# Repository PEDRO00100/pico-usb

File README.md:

> [!WARNING]
> ### ⚠️ LEGAL DISCLAIMER & TERMS OF USE
> 
> This hardware device, firmware, and its accompanying software suite are developed and provided **strictly for educational purposes, authorized laboratory environments, and professional security auditing.**
> 
> By building, accessing, or utilizing this tool, you acknowledge and agree to the following:
> 
> * **Authorized Use Only:** You must obtain explicit, written consent from the infrastructure or system owner before engaging in any security testing, payload injection, or assessment.
> * **No Liability:** The creators, contributors, and maintainers of this project assume **absolute no liability** and are not responsible for any direct or indirect damage, data loss, misuse, or illegal activities resulting from the deployment of this device.
> * **End-User Responsibility:** It is solely your responsibility to ensure compliance with all applicable local, state, and federal laws. Any use of this tool for malicious intent, unauthorized access, or covert data exfiltration is strictly prohibited.

## ⚙️ System Architecture & Operation

This project is a hardware-based security auditing and penetration testing tool (HID Injection Engine) built around the **RP2040** microcontroller. Unlike traditional USB injection scripts that require hardcoding and recompiling firmware for every assessment, this device operates as an autonomous, dynamic execution engine. It reads attack scripts directly from an external MicroSD card and allows instant, on-the-fly selection of up to 16 different payloads via hardware switching.

---

### 1. Hardware & Peripheral Mapping

The PCB layout is engineered for signal integrity, prioritizing short trace lengths for high-speed SPI bus lines while keeping digital control switches isolated. The GPIO pin assignment on the RP2040 is structured as follows:

| Physical Peripheral | RP2040 Pin | System Function / Role | Electrical Logic |
| :--- | :---: | :--- | :--- |
| **Setup Mode Switch (`GP0/DEV`)** | `GP0` | Toggles between Development Mode & Attack Mode | Internal Pull-Up (`GND = Dev`) |
| **DIP Switch (Bit 0 - LSB)** | `GP2` | Binary Payload Selector (`payload1Pin` / `SWD-1`) | Active-Low (`GND = 1`) |
| **DIP Switch (Bit 1)** | `GP3` | Binary Payload Selector (`payload2Pin` / `SWD-2`) | Active-Low (`GND = 1`) |
| **DIP Switch (Bit 2)** | `GP4` | Binary Payload Selector (`payload3Pin` / `SWD-3`) | Active-Low (`GND = 1`) |
| **DIP Switch (Bit 3 - MSB)** | `GP5` | Binary Payload Selector (`payload4Pin` / `SWD-4`) | Active-Low (`GND = 1`) |
| **MicroSD SPI (MISO)** | `GP16` | Data receive from external storage | SPI0 Bus |
| **MicroSD SPI (CS)** | `GP17` | Chip Select / SD card activation | Digital Output |
| **MicroSD SPI (SCK)** | `GP18` | Bus clock synchronization | SPI0 Bus |
| **MicroSD SPI (MOSI)** | `GP19` | Data transmit to external storage | SPI0 Bus |

*(Note: Additional GPIO pins such as `GP22` are routed on the PCB layout for secondary applications or future expansion, but are omitted from active execution loops to streamline automated payload delivery).*

#### 🔘 Onboard Physical Control Buttons
The device incorporates three dedicated tactile buttons for system management and firmware operations:
* **`BOOTSEL` Button:** Connected directly to the RP2040 bootrom interface. Holding this button while plugging the device into a host forces entry into USB Mass Storage bootloader mode for flashing or updating the core CircuitPython firmware (`.uf2` files).
* **`RUN` / `RST` Button:** Triggers a hard electrical reset of the RP2040 microcontroller without needing to physically unplug the USB connector, enabling rapid rebooting after switching payloads.
* **`DEV MODE` Button (`GP0`):** Pulls `GP0` to ground (`GND`). When engaged during boot, it prevents automated payload execution and mounts the internal `CIRCUITPY` drive for safe script editing.

#### 🔌 Dual-Head USB Interface & Protection
The hardware features a versatile **Dual-Head USB architecture**, integrating both **USB-A** and **USB-C** connectors directly onto the PCB edge. This allows native insertion into legacy desktops, modern laptops, servers, and mobile devices without requiring external adapters. 
* **ESD Protection:** The data lines (`D+` / `D-`) include onboard electrical protections and transient voltage suppression to safeguard the microcontroller against static discharges during rapid field insertion.
* **⚠️ Critical Safety Rule:** The dual connectors share the same internal USB data bus. **Never connect both USB-A and USB-C ports simultaneously to two different host devices or power sources**, as this could cause bus contention or electrical back-feeding.

---

### 2. Binary Payload Selector (4-Bit DIP Switch)

To eliminate the need for reprogramming the device between different engagement scenarios, the board features an onboard 4-position DIP switch (`A6H-4101`) operating on **pure binary decoding**.

Each switch pin is configured with internal pull-up resistors (Active-Low logic). Moving a switch to the **ON** position bridges the circuit to Ground (`GND`), which the firmware decodes as a logical `1` for that specific bit position.

```text
Bit 3 (MSB)   Bit 2       Bit 1       Bit 0 (LSB)
  [GP5]       [GP4]       [GP3]       [GP2]
  Value: 8    Value: 4    Value: 2    Value: 1

```

* **Combination `0000` (All OFF):** Executes the default script located at `/sd/payload.dd`.
* **Combinations `0001` through `1111` (1 to 15):** Sums the active bit values in powers of 2 and dynamically routes execution to the numbered script on the MicroSD card (from `/sd/payload1.dd` up to `/sd/payload15.dd`).

---

### 3. Operating Modes & USB Stealth Spoofing

The USB enumeration profile is strictly managed by `boot.py` **before** the target operating system (Windows, macOS, or Linux) initializes the peripheral. The operating mode is governed by the state of the `GP0` tactile button/switch:

#### 🟢 Development Mode (`GP0` connected to GND)

* **Purpose:** Script editing, live debugging, and system maintenance.
* **USB Profile:** Habilitates standard USB Mass Storage (exposing the internal `CIRCUITPY` drive), Serial CDC (REPL console), and HID keyboard interfaces. Automated attack execution is safely bypassed.

#### 🔴 Attack / Stealth Mode (`GP0` floating / Unpressed)

* **Purpose:** Active field auditing and Endpoint Detection & Response (EDR / DLP) evasion.
* **USB Profile:** The firmware executes `storage.disable_usb_drive()`, completely hiding internal Flash memory from the host OS and disabling Serial/MIDI endpoints (`usb_cdc.disable()`, `usb_midi.disable()`).
* **Identity Spoofing:** To prevent triggering vendor-specific blocklists while adhering to safe open-source distribution standards (BYOC - *Bring Your Own Configuration*), the device overrides its hardware descriptors using the open community VID **`0x1209`** (pid.codes) and generic keyboard PID **`0x0001`**:

```python
# Hardware descriptor override defined in boot.py
supervisor.set_usb_identification(
    vid=0x1209,         # Open-Source Community VID (pid.codes)
    pid=0x0001,         # Generic Keyboard PID
    manufacturer="Generic",
    product="USB Keyboard"
)

```

> ⚠️ **Tactical Advantage:** When plugged into a host system in Attack Mode, the operating system **strictly enumerates a generic HID USB Keyboard**. No storage drives are mounted, no COM ports appear in Device Manager, and no Raspberry Pi / Adafruit hardware signatures are exposed.

---

### 4. Asynchronous Execution Engine & Resilience

The core execution engine (`code.py`) is built around asynchronous event loops (`asyncio`). This allows the microcontroller to handle concurrent background tasks—such as button debouncing, filesystem polling, and monitoring host keyboard lock LEDs (Caps/Num/Scroll Lock) for data exfiltration—without causing latency or blocking keystroke injection.

To guarantee field reliability and prevent kernel panics during live deployments, the firmware implements multiple defensive architecture layers:

1. **Zero-RAM Allocation Filesystem Polling:** To check for the presence of payload files on the MicroSD card without fragmenting the microcontroller's limited heap memory, the engine avoids memory-heavy directory listings (`os.listdir()`). Instead, it performs direct, low-overhead FAT32 metadata queries using `os.stat()`.
2. **3-Tier Fallback Routing:** If an indexed script cannot be read, the execution pipeline gracefully degrades through three safety tiers to ensure the assessment does not fail silently:
* *Tier 1:* Attempts to execute the exact binary path selected by the DIP switch (e.g., `/sd/payload5.dd`).
* *Tier 2:* If the target file is missing, it falls back automatically to the standard default script (`/sd/payload.dd`).
* *Tier 3:* If the default script is also missing, it performs an emergency scan of the MicroSD card root and executes the first available `.dd` payload found.

3. **Hardware Kill-Switch:** During the boot sequence, if the engine detects a file named `loot.bin` in the root directory, it immediately aborts all keystroke injection routines to prevent accidental exfiltration overrides or execution loops.

## 💾 Firmware & Software Installation Guide

Setting up the device is divided into two straightforward phases: flashing the base interpreter (CircuitPython) and loading the attack and decoding engine. Once this process is complete, the microcontroller's execution logic will be permanently configured.

---

### Step 1: Installing the Core Engine (CircuitPython)

To enable the RP2040 microcontroller to interpret attack scripts in real time, you must install the base CircuitPython firmware:

1. **Bootloader Mode:** Press and hold the onboard **`BOOTSEL`** physical button while plugging the USB cable into your computer.
2. **RPI-RP2 Drive:** Release the button once plugged in. Your operating system will automatically mount a mass storage drive named `RPI-RP2`.
3. **Flashing:** Download the latest official release of **CircuitPython 10.x** (`.uf2` file format) for the Raspberry Pi Pico / RP2040 and drag the file directly into the `RPI-RP2` drive.
4. **Automatic Reboot:** Once the copy completes, the drive will automatically eject, and the microcontroller will reboot, creating a new flash drive named **`CIRCUITPY`**.

---

### Step 2: Loading the Attack Engine & Dependencies

Once the `CIRCUITPY` drive is available, you must transfer the core operating logic and hardware libraries. Navigate to the `Software/` directory within this repository, which contains the exact system package:

```text
Software/
├── boot.py             # Hardware USB Profile & Stealth Spoofing Manager
├── boot_out.txt        # System boot log (Auto-generated by CircuitPython)
├── code.py             # Asynchronous Core Kernel & Execution Loop
├── duckyinpython.py    # DuckyScript Parser & Payload Execution Engine
├── lib/                # Required CircuitPython libraries (HID, Debouncer, etc.)
├── LICENSE             # GPLv2 License
├── pins.py             # Hardware GPIO Pin Mapping & DIP Switch Config
├── sd/                 # Example payload directory (For external MicroSD card)
└── settings.toml       # Runtime configuration file

```

#### 📦 File Transfer Protocol:

1. **Internal Flash (`CIRCUITPY` drive):**
* Select and copy all core Python scripts (`boot.py`, `code.py`, `duckyinpython.py`, `pins.py`, `settings.toml`, and `LICENSE`).
* **⚠️ CRITICAL - The `lib/` folder:** You **must** copy the entire **`lib/`** directory into the root of the `CIRCUITPY` drive. This folder contains essential drivers (`adafruit_hid`, `adafruit_debouncer`, etc.) required for keystroke injection and tactile button reading.
* *(Note: You can ignore `boot_out.txt`, as the microcontroller will automatically regenerate this log file on its next boot).*

2. **External Storage (MicroSD Card):**
* Take the contents inside the **`sd/`** folder (e.g., your `.dd` payload files) and copy them directly to the root of your FAT32-formatted **MicroSD card**.
* Insert the MicroSD card into the onboard SPI slot (`J3`). When the RP2040 boots, `code.py` will automatically mount this physical card at the `/sd` system path.

---

### Step 3: Access Management & Safe Mode (Critical!)

As soon as the system files are copied over, `boot.py` will take absolute control of the board's USB interfaces on every subsequent boot. It is crucial to understand the following tactical behavior before unplugging the cable:

> 🚨 **AUTOMATIC INJECTION WARNING:**
> From this moment forward, **every time you plug the device into a USB port normally, it will boot in Attack Mode (Stealth Mode)**. This means the `CIRCUITPY` drive will completely disappear from your operating system, and the payload selected via the DIP switch on the MicroSD card **will execute automatically and immediately**.

#### 🛠️ How to re-access the `CIRCUITPY` drive to edit code?

To prevent the attack script from triggering and to mount the internal storage drive back onto your computer (e.g., to debug code or update core scripts), you must engage the hardware safety override:

1. **Press and hold the `DEV MODE` (`GP0`) button** on the board.
2. While holding the button down, **plug the USB cable** into your computer.
3. Once plugged in, you can safely release the button.
4. **Result:** The microcontroller detects the ground connection on pin `GP0`, aborts automated payload execution, and safely exposes the `CIRCUITPY` drive and Serial REPL console on your screen in safe development mode.

## 🛠️ Hardware Compatibility & DIY Protoboard Build

While this project features a custom-designed, dedicated PCB with integrated dual-head USB connectors and ESD protection, the core software suite is **100% compatible with standard, off-the-shelf Raspberry Pi Pico** boards (or any generic RP2040 development board running CircuitPython).

If you are prototyping on a breadboard or building a custom DIY injection tool using an original Raspberry Pi Pico, you can deploy this firmware without modifying a single line of code. You simply need to manually wire the external modules according to the hardware mapping defined in `pins.py`:

### 📌 DIY Wiring Checklist for Standard Pico:
* **MicroSD Card Module:** Wire a 3.3V SPI MicroSD breakout board directly to the RP2040's **SPI0 bus** (`MISO` -> `GP16`, `CS` -> `GP17`, `SCK` -> `GP18`, and `MOSI` -> `GP19`).
* **4-Bit Binary DIP Switch:** Connect four mechanical switches (or simple jumper wires) between ground (`GND`) and pins **`GP2`**, **`GP3`**, **`GP4`**, and **`GP5`**. When closed (grounded), the internal pull-up resistor drops to `0V`, which the software decodes as an active binary `1`.
* **Development Mode Safety Jumper (`GP0`):** You **must** wire a tactile button or jumper wire between **`GP0`** and **`GND`**. This is critical: without this physical override, an off-the-shelf Pico will permanently boot in Stealth Attack Mode, hiding the USB drive and locking you out of the REPL console.

---

## 📂 MicroSD Payload Structure & Binary Mapping

The execution engine searches the root directory of the FAT32-formatted MicroSD card for standard DuckyScript (`.dd`) payload files. To utilize the hardware DIP switch, name your scripts following this exact binary convention:

| DIP Switch State (`SW4` -> `SW1`) | Binary Value | Target Payload Path | Description / Engagement Use Case |
| :---: | :---: | :--- | :--- |
| `OFF` · `OFF` · `OFF` · `OFF` | `0000` (0) | `/sd/payload.dd` | Default fallback / Standard assessment payload |
| `OFF` · `OFF` · `OFF` · `ON`  | `0001` (1) | `/sd/payload1.dd` | Quick reconnaissance / System info enumeration |
| `OFF` · `OFF` · `ON`  · `OFF` | `0010` (2) | `/sd/payload2.dd` | Remote access staging / Reverse shell |
| `...` · `...` · `...` · `...` | `1 to 14`  | `/sd/payload3.dd` to `14.dd` | Custom specialized audit scripts |
| `ON`  · `ON`  · `ON`  · `ON`  | `1111` (15)| `/sd/payload15.dd`| Emergency cleanup / Anti-forensic routine |

> 💡 **Tactical Fallback Note:** If you dial a specific binary combination on the DIP switch (e.g., index `5`) but forget to load `/sd/payload5.dd` onto the MicroSD card, the asynchronous engine will not crash. It automatically downgrades to Tier-2 fallback and executes `/sd/payload.dd`, guaranteeing that your field engagement never fails silently.

---

## 📸 Board Designs & Renders

3D renders and PCB layer routing for the **Pico-USB** board.

<table align="center">
  <tr>
    <td align="center">
      <br/>
      <sub><b>3D Front</b></sub>
    </td>
    <td align="center">
      <br/>
      <sub><b>3D Back</b></sub>
    </td>
    <td align="center">
      <br/>
      <sub><b>2D F.Cu</b></sub>
    </td>
    <td align="center">
      <br/>
      <sub><b>2D B.Cu</b></sub>
    </td>
  </tr>
</table>

---

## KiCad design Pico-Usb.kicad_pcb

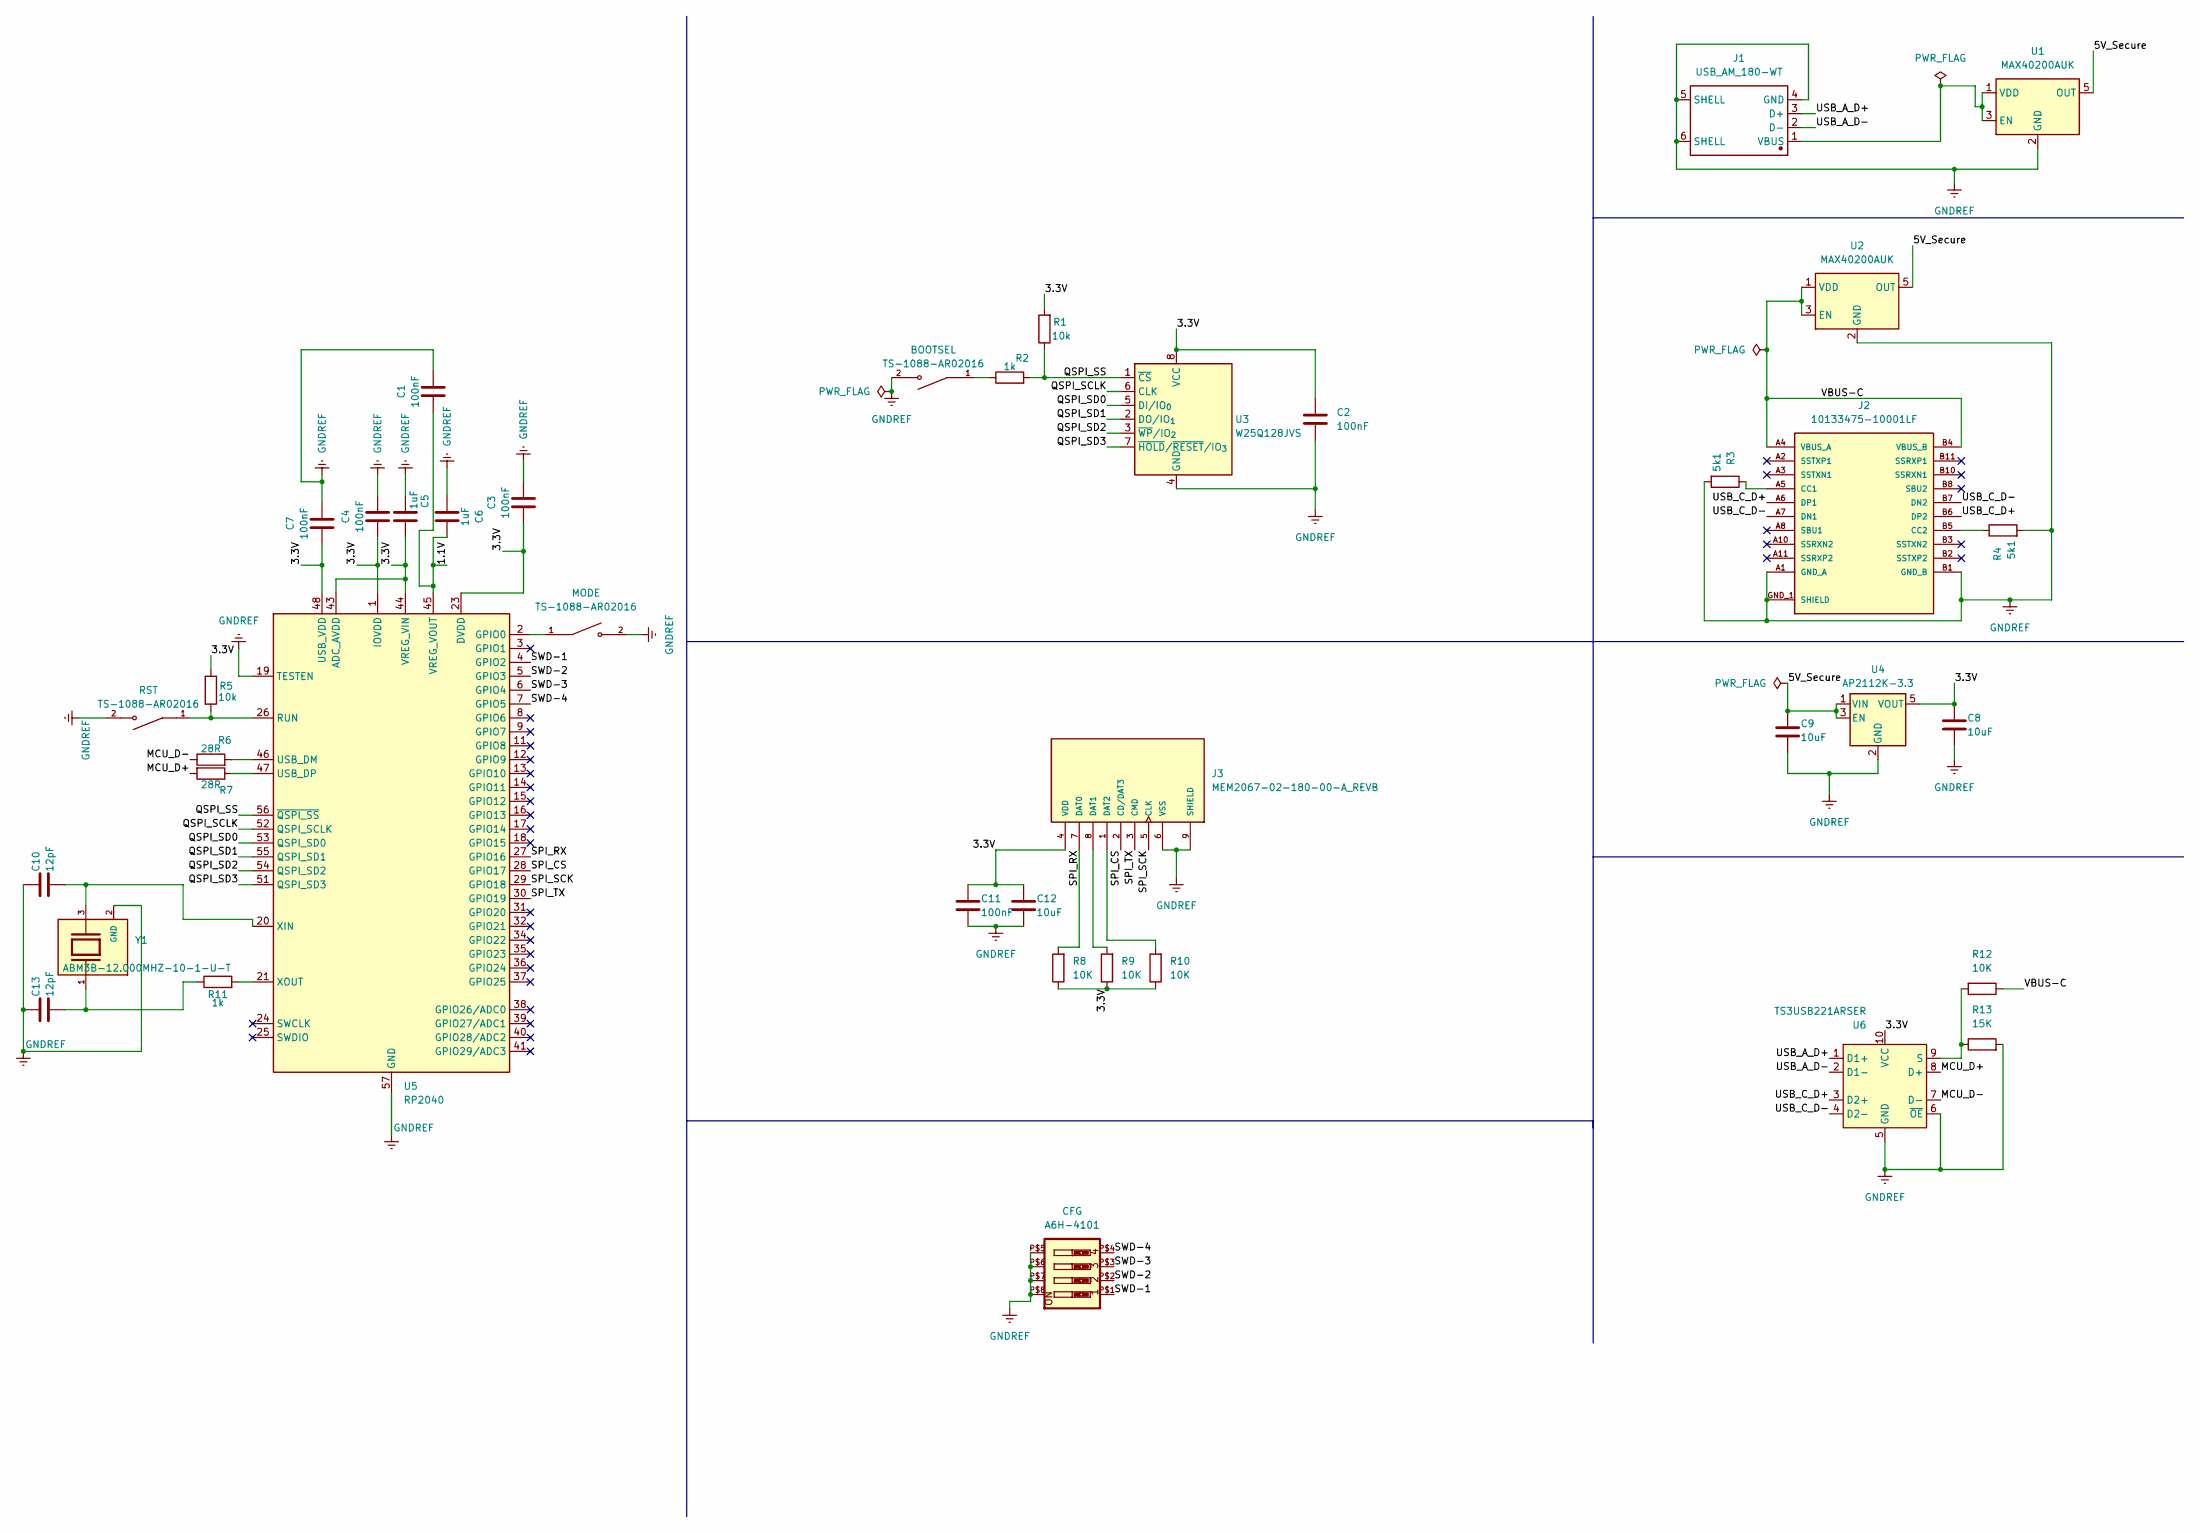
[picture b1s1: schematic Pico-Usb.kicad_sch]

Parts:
BOOTSEL: TS-1088-AR02016; SW_TS-1088-AR02016; PARTREV N/A
C1, C2, C3, C4, C7, C11: 100nF; C_0402_1005Metric
C5, C6: 1uF; C_0402_1005Metric
C8, C9, C12: 10uF; C_0402_1005Metric
C10, C13: 12pF; C_0402_1005Metric
CFG: A6H-4101; A6H-410X
J1: USB_AM_180-WT; USB-AM-180-WT
J2: 10133475-10001LF; Amphenol_USBC_Plug; PARTREV C
J3: MEM2067-02-180-00-A_REVB; GCT_MEM2067-02-180-00-A_REVB
MODE: TS-1088-AR02016; SW_TS-1088-AR02016; PARTREV N/A
R1, R5: 10k; R_0402_1005Metric
R2, R11: 1k; R_0402_1005Metric
R3, R4: 5k1; R_0402_1005Metric
R6, R7: 28R; R_0402_1005Metric
R8, R9, R10, R12: 10K; R_0402_1005Metric
R13: 15K; R_0402_1005Metric
RST: TS-1088-AR02016; SW_TS-1088-AR02016; PARTREV N/A
U1, U2: MAX40200AUK; SOT-23-5
U3: W25Q128JVS; SOIC-8_5.3x5.3mm_P1.27mm
U4: AP2112K-3.3; SOT-23-5
U5: RP2040; QFN-56-1EP_7x7mm_P0.4mm_EP3.2x3.2mm
U6: TS3USB221ARSER; TS3USB221
Y1: ABM3B-12.000MHZ-10-1-U-T; XTAL_ABM3B-12.000MHZ-10-1-U-T; PARTREV 08.25.15

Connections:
/1.1V: C1.1, C6.1, U5.45 (VREG_VOUT)
/3.3V: C2.1, C3.1, C4.1, C5.1, C7.1, C8.1, C11.1, C12.1, J3.4 (VDD), R1.2, R5.1, R8.1, R9.1, R10.1, U3.8 (VCC), U4.5 (VOUT), U5.1 (IOVDD), U5.10 (IOVDD), U5.22 (IOVDD), U5.23 (DVDD), U5.33 (IOVDD), U5.42 (IOVDD), U5.43 (ADC_AVDD), U5.44 (VREG_VIN), U5.48 (USB_VDD), U5.49 (IOVDD), U5.50 (DVDD), U6.10 (VCC)
/5V_Secure: C9.1, U1.5 (OUT), U2.5 (OUT), U4.1 (VIN), U4.3 (EN)
/MCU_D+: R7.2, U6.8 (D+)
/MCU_D-: R6.1, U6.7 (D-)
/QSPI_SCLK: U3.6 (CLK), U5.52 (QSPI_SCLK)
/QSPI_SD0: U3.5 (DI/IO_{0}), U5.53 (QSPI_SD0)
/QSPI_SD1: U3.2 (DO/IO_{1}), U5.55 (QSPI_SD1)
/QSPI_SD2: U3.3 (~WP/IO_{2}), U5.54 (QSPI_SD2)
/QSPI_SD3: U3.7 (~HOLD/~RESET/IO_{3}), U5.51 (QSPI_SD3)
/QSPI_SS: R1.1, R2.2, U3.1 (~CS), U5.56 (~QSPI_SS)
/SPI_CS: J3.2 (CD/DAT3), U5.28 (GPIO17)
/SPI_RX: J3.7 (DAT0), R8.2, U5.27 (GPIO16)
/SPI_SCK: J3.5 (CLK), U5.29 (GPIO18)
/SPI_TX: J3.3 (CMD), U5.30 (GPIO19)
/SWD-1: CFG.P$1, U5.4 (GPIO2)
/SWD-2: CFG.P$2, U5.5 (GPIO3)
/SWD-3: CFG.P$3, U5.6 (GPIO4)
/SWD-4: CFG.P$4, U5.7 (GPIO5)
/USB_A_D+: J1.3 (D+), U6.1 (D1+)
/USB_A_D-: J1.2 (D-), U6.2 (D1-)
/USB_C_D+: J2.A6 (DP1), J2.B6 (DP2), U6.3 (D2+)
/USB_C_D-: J2.A7 (DN1), J2.B7 (DN2), U6.4 (D2-)
GNDREF: BOOTSEL.2, C1.2, C2.2, C3.2, C4.2, C5.2, C6.2, C7.2, C8.2, C9.2, C10.1, C11.2, C12.2, C13.1, CFG.P$5, CFG.P$6, CFG.P$7, CFG.P$8, J1.4 (GND), J1.5 (SHELL), J1.6 (SHELL), J2.A1 (GND_A), J2.A12 (GND_A), J2.B1 (GND_B), J2.B12 (GND_B), J2.GND_1 (SHIELD), J2.GND_2 (SHIELD), J3.6 (VSS), J3.9 (SHIELD), J3.10 (SHIELD), J3.11 (SHIELD), J3.12 (SHIELD), MODE.2, R3.2, R4.2, R13.2, RST.2, U1.2 (GND), U2.2 (GND), U3.4 (GND), U4.2 (GND), U5.19 (TESTEN), U5.57 (GND), U6.5 (GND), U6.6 (~OE), Y1.2 (GND), Y1.4 (GND)
unnamed: BOOTSEL.1, R2.1
unnamed: C13.2, R11.1, Y1.1
unnamed: J2.A5 (CC1), R3.1
unnamed: J2.B5 (CC2), R4.1
unnamed: J3.8 (DAT1), R9.2
unnamed: J3.1 (DAT2), R10.2
unnamed: J1.1 (VBUS), U1.1 (VDD), U1.3 (EN)
unnamed: MODE.1, U5.2 (GPIO0)
unnamed: R5.2, RST.1, U5.26 (RUN)
unnamed: R6.2, U5.46 (USB_DM)
unnamed: R7.1, U5.47 (USB_DP)
unnamed: C10.2, U5.20 (XIN), Y1.3
unnamed: R11.2, U5.21 (XOUT)
unnamed: R12.2, R13.1, U6.9 (S)
VBUS_A: J2.A4 (VBUS_A), J2.A9 (VBUS_A), J2.B4 (VBUS_B), J2.B9 (VBUS_B), R12.1, U2.1 (VDD), U2.3 (EN)

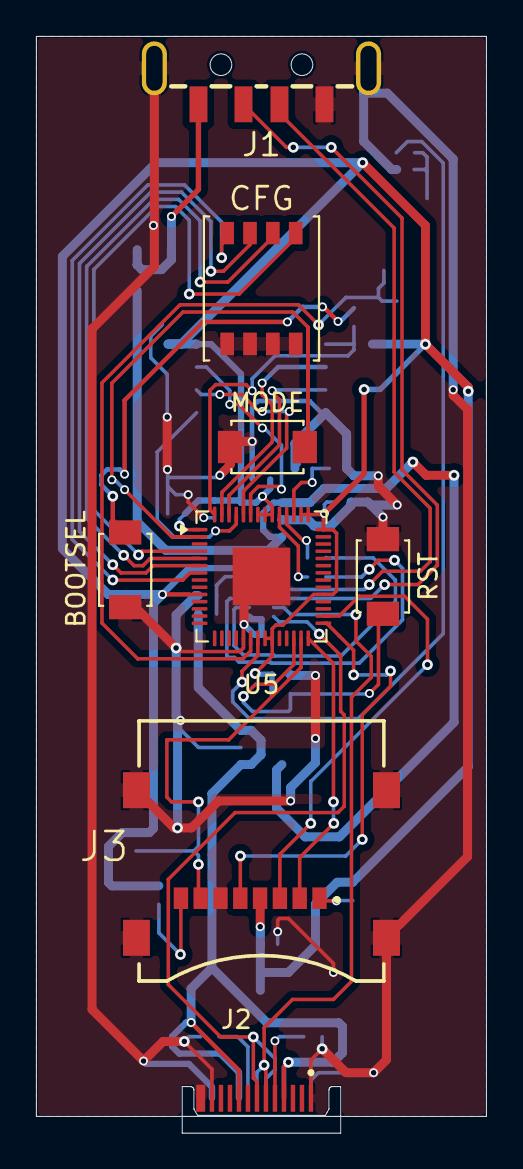
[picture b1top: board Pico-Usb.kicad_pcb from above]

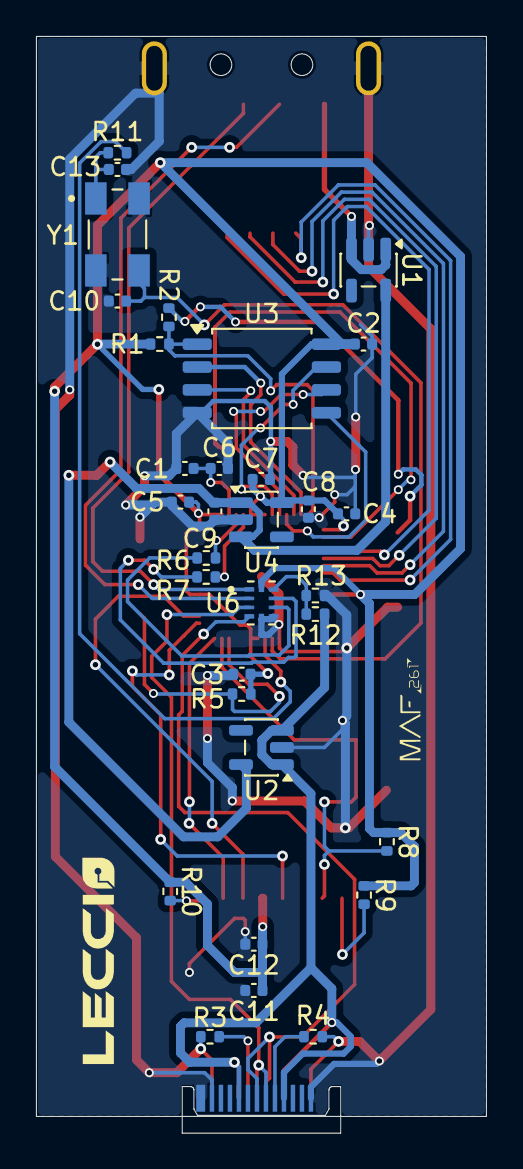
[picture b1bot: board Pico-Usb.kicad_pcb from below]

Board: 2 copper layers, 25.0 x 60.9 mm, 40 parts (32 on the bottom side), 39 nets.
